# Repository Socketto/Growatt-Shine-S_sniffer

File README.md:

# Growatt SPH Inverter Communication Sniffer

## Project Overview

This project aims to develop a custom hardware interface and software system for reading and interpreting communication data from a **Growatt SPH series inverter**. The system intercepts the communication between the inverter and the official **ShineWiFi-S dongle**, using signal conversion and a **Raspberry Pi** to capture and decode the **Modbus RTU protocol** used by Growatt.

## System Architecture

The solution is composed of the following main stages:

1. **Sniffing the RS-232 Communication**  
   The inverter and ShineWiFi-S dongle communicate over an **RS-232 serial connection**. This project taps into that communication without interfering with the normal operation of either device.

2. **RS-232 to TTL Conversion**  
   Because RS-232 voltage levels are not directly compatible with most microcontrollers or logic analyzers, the tapped signal is first converted to **TTL level signals** using an RS-232 to TTL converter module (MAX232).

3. **TTL to RS-485 Conversion**  
   To ensure signal integrity over longer distances and allow for differential signaling, the TTL signal is then converted to **RS-485** using a TTL to RS-485 transceiver (MAX485).

4. **Data Acquisition via Raspberry Pi**  
   The RS-485 output is connected to a **Raspberry Pi**, which acts as the main controller. The Raspberry Pi receives the data through its serial interface.

5. **Modbus Decoding and Data Interpretation**  
   A **Python script** running on the Raspberry Pi listens to the serial port, decodes the Modbus RTU frames, and extracts relevant data such as:

   - Inverter status
   - Power production
   - Battery charge/discharge
   - Grid voltage and frequency
   - And other available telemetry

## Hardware Components

- Growatt SPH series inverter
- ShineWiFi-S dongle (OEM)
- Breakout DB9
- Raspberry Pi (any model with UART support)
- Optional: Logic level shifters and protective diodes

## Key Advantages

- **Non-intrusive monitoring** of Growatt inverter communication
- **Real-time access** to detailed inverter data
- Enables custom logging, alerting, or integration with home automation platforms (e.g., Home Assistant)

## Disclaimer

This project involves tapping into proprietary communication and working with high voltages indirectly. **Ensure all safety precautions are followed** and use this project at your own risk. This is intended for **educational and personal use only**.

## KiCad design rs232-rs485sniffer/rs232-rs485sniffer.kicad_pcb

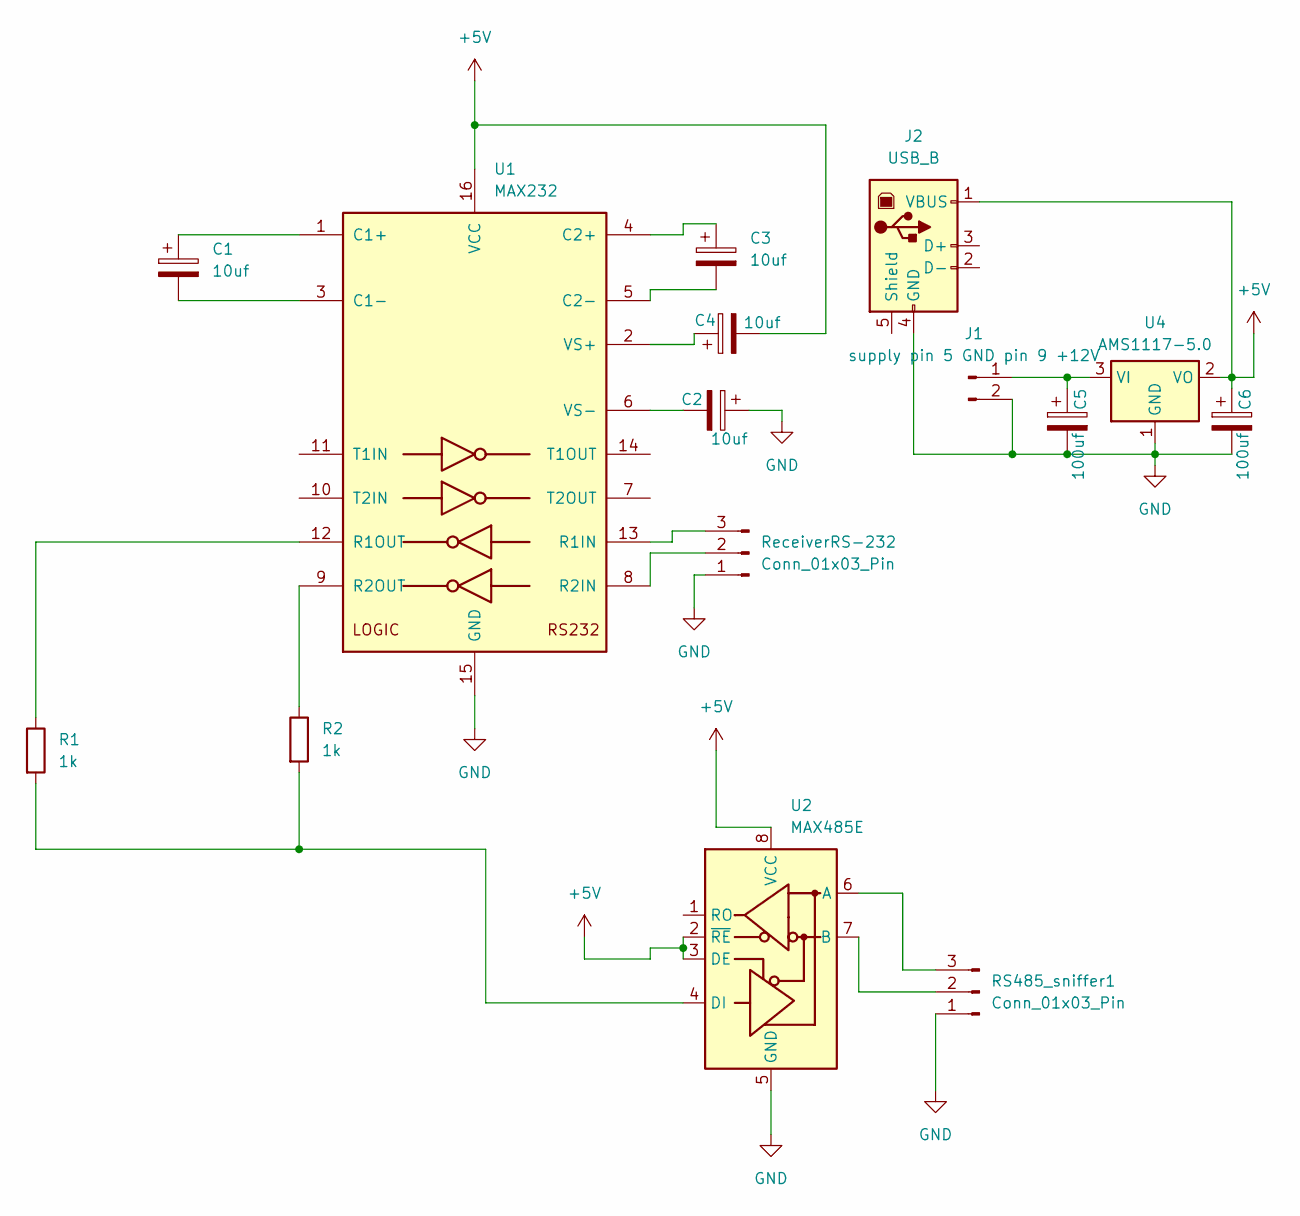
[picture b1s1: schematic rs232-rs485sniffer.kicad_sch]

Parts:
C1, C2, C3, C4: 10uf; CP_Radial_D8.0mm_P3.80mm
C5, C6: 100uf; CP_Radial_D8.0mm_P3.80mm
J1: supply pin 5 GND pin 9 +12V; TerminalBlock_Phoenix_MKDS-1,5-2_1x02_P5.00mm_Horizontal
J2: USB_B; USB_B_Lumberg_2411_02_Horizontal
R1, R2: 1k; L_1206_3216Metric_Pad1.22x1.90mm_HandSolder
RS485_sniffer1: Conn_01x03_Pin; TerminalBlock_Phoenix_MKDS-1,5-3-5.08_1x03_P5.08mm_Horizont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
ReceiverRS-232: Conn_01x03_Pin; TerminalBlock_Phoenix_MKDS-1,5-3-5.08_1x03_P5.08mm_Horizont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
U1: MAX232; DIP-16_W7.62mm_Socket_LongPads
U2: MAX485E; SOIC-8_3.9x4.9mm_P1.27mm
U4: AMS1117-5.0; SOT-223-3_TabPin2

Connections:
+5V: C4.2, C6.1, J2.1 (VBUS), U1.16 (VCC), U2.2 (~RE), U2.3 (DE), U2.8 (VCC), U4.2 (VO)
GND: C2.1, C5.2, C6.2, J1.2, J2.4 (GND), RS485_sniffer1.1, ReceiverRS-232.1, U1.15 (GND), U2.5 (GND), U4.1 (GND)
unnamed: C5.1, J1.1, U4.3 (VI)
unnamed: RS485_sniffer1.2, U2.7 (B)
unnamed: RS485_sniffer1.3, U2.6 (A)
unnamed: ReceiverRS-232.2, U1.8 (R2IN)
unnamed: ReceiverRS-232.3, U1.13 (R1IN)
unnamed: C1.1, U1.1 (C1+)
unnamed: C1.2, U1.3 (C1-)
unnamed: C3.1, U1.4 (C2+)
unnamed: C3.2, U1.5 (C2-)
unnamed: R1.1, U1.12 (R1OUT)
unnamed: R2.1, U1.9 (R2OUT)
unnamed: C4.1, U1.2 (VS+)
unnamed: C2.2, U1.6 (VS-)
unnamed: R1.2, R2.2, U2.4 (DI)

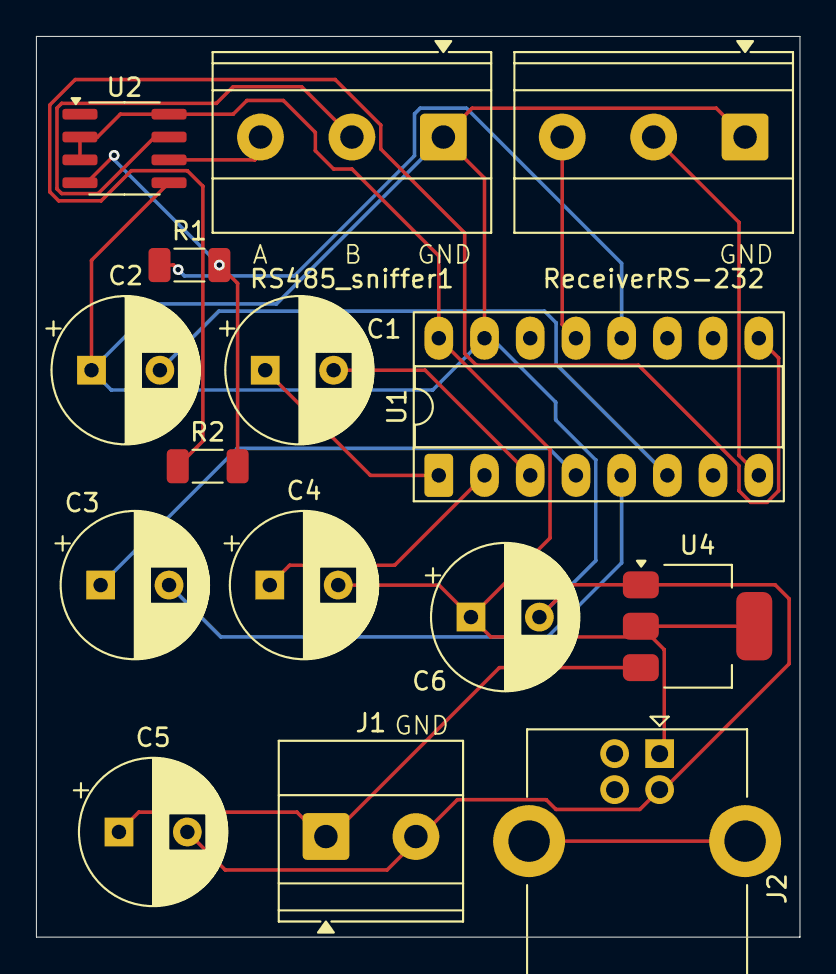
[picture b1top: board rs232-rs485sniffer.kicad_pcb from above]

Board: 2 copper layers, 42.4 x 50.0 mm, 15 parts (0 on the bottom side), 16 nets.

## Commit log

2025-07-02 [FIRST] First draft of board to convert signal RS-232 in RS-485 signals
2025-07-03 [ADD] Add board and add management with unique rs-485 transceiver
2025-07-04 [UPD] Update schematic and add docs
2025-07-04 [FIX] Add complete board v1 with gerber file
2025-07-04 [ADD] Add readme
2025-07-07 [ADD] Add 2 resistor to moderate signal of TTL
2025-07-17 [FIX] Stable version
